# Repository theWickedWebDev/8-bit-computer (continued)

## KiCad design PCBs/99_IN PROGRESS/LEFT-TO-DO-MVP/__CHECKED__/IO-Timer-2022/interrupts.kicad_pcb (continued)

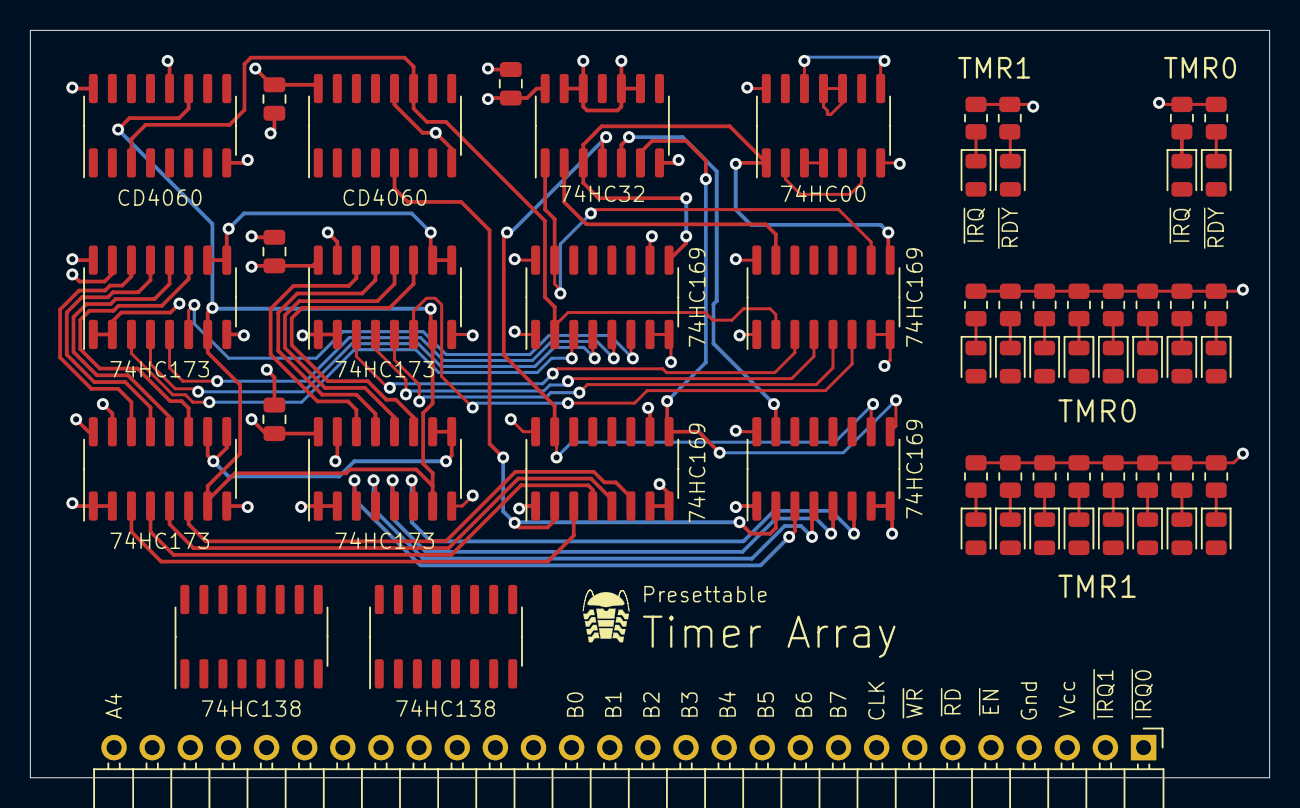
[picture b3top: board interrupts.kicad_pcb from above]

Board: 4 copper layers, 82.5 x 49.8 mm, 59 parts (0 on the bottom side), 83 nets.

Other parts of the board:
U9, U14: CD4060; SOIC-16_3.9x9.9mm_P1.27mm
U10, U11: 74LS173; SOIC-16_3.9x9.9mm_P1.27mm

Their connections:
/Reload Value Register/RELOAD0: U10.3 (Q0); also elsewhere on the board
/Reload Value Register/RELOAD1: U10.4 (Q1); also elsewhere on the board
/Reload Value Register/RELOAD2: U10.5 (Q2); also elsewhere on the board
/Reload Value Register/RELOAD3: U10.6 (Q3); also elsewhere on the board
/Reload Value Register/RELOAD4: U11.3 (Q0); also elsewhere on the board
/Reload Value Register/RELOAD5: U11.4 (Q1); also elsewhere on the board
/Reload Value Register/RELOAD6: U11.5 (Q2); also elsewhere on the board
/Reload Value Register/RELOAD7: U11.6 (Q3); also elsewhere on the board
BUS0: U10.14 (D0); also elsewhere on the board
BUS1: U10.13 (D1); also elsewhere on the board
BUS2: U10.12 (D2); also elsewhere on the board
BUS3: U10.11 (D3); also elsewhere on the board
BUS4: U11.14 (D0); also elsewhere on the board
BUS5: U11.13 (D1); also elsewhere on the board
BUS6: U11.12 (D2); also elsewhere on the board
BUS7: U11.11 (D3); also elsewhere on the board
CPU_CLOCK: U9.11 (I), U10.7 (Cp), U11.7 (Cp); also elsewhere on the board
GND: U9.8 (GND), U9.12 (RESET), U10.1 (Oe1), U10.2 (Oe2), U10.8 (GND), U10.15 (Mr), U11.1 (Oe1), U11.2 (Oe2), U11.8 (GND), U11.15 (Mr), U14.8 (GND), U14.12 (RESET); also elsewhere on the board
VCC: U9.16 (VCC), U10.16 (VCC), U11.16 (VCC), U14.16 (VCC); also elsewhere on the board
~SCLK8192: U9.3 (Q14), U14.11 (I); also elsewhere on the board
~SCLK131072: U14.5 (Q5); also elsewhere on the board
~SET_RELOAD_VALUE0: U10.9 (E1), U10.10 (E2), U11.9 (E1), U11.10 (E2); also elsewhere on the board

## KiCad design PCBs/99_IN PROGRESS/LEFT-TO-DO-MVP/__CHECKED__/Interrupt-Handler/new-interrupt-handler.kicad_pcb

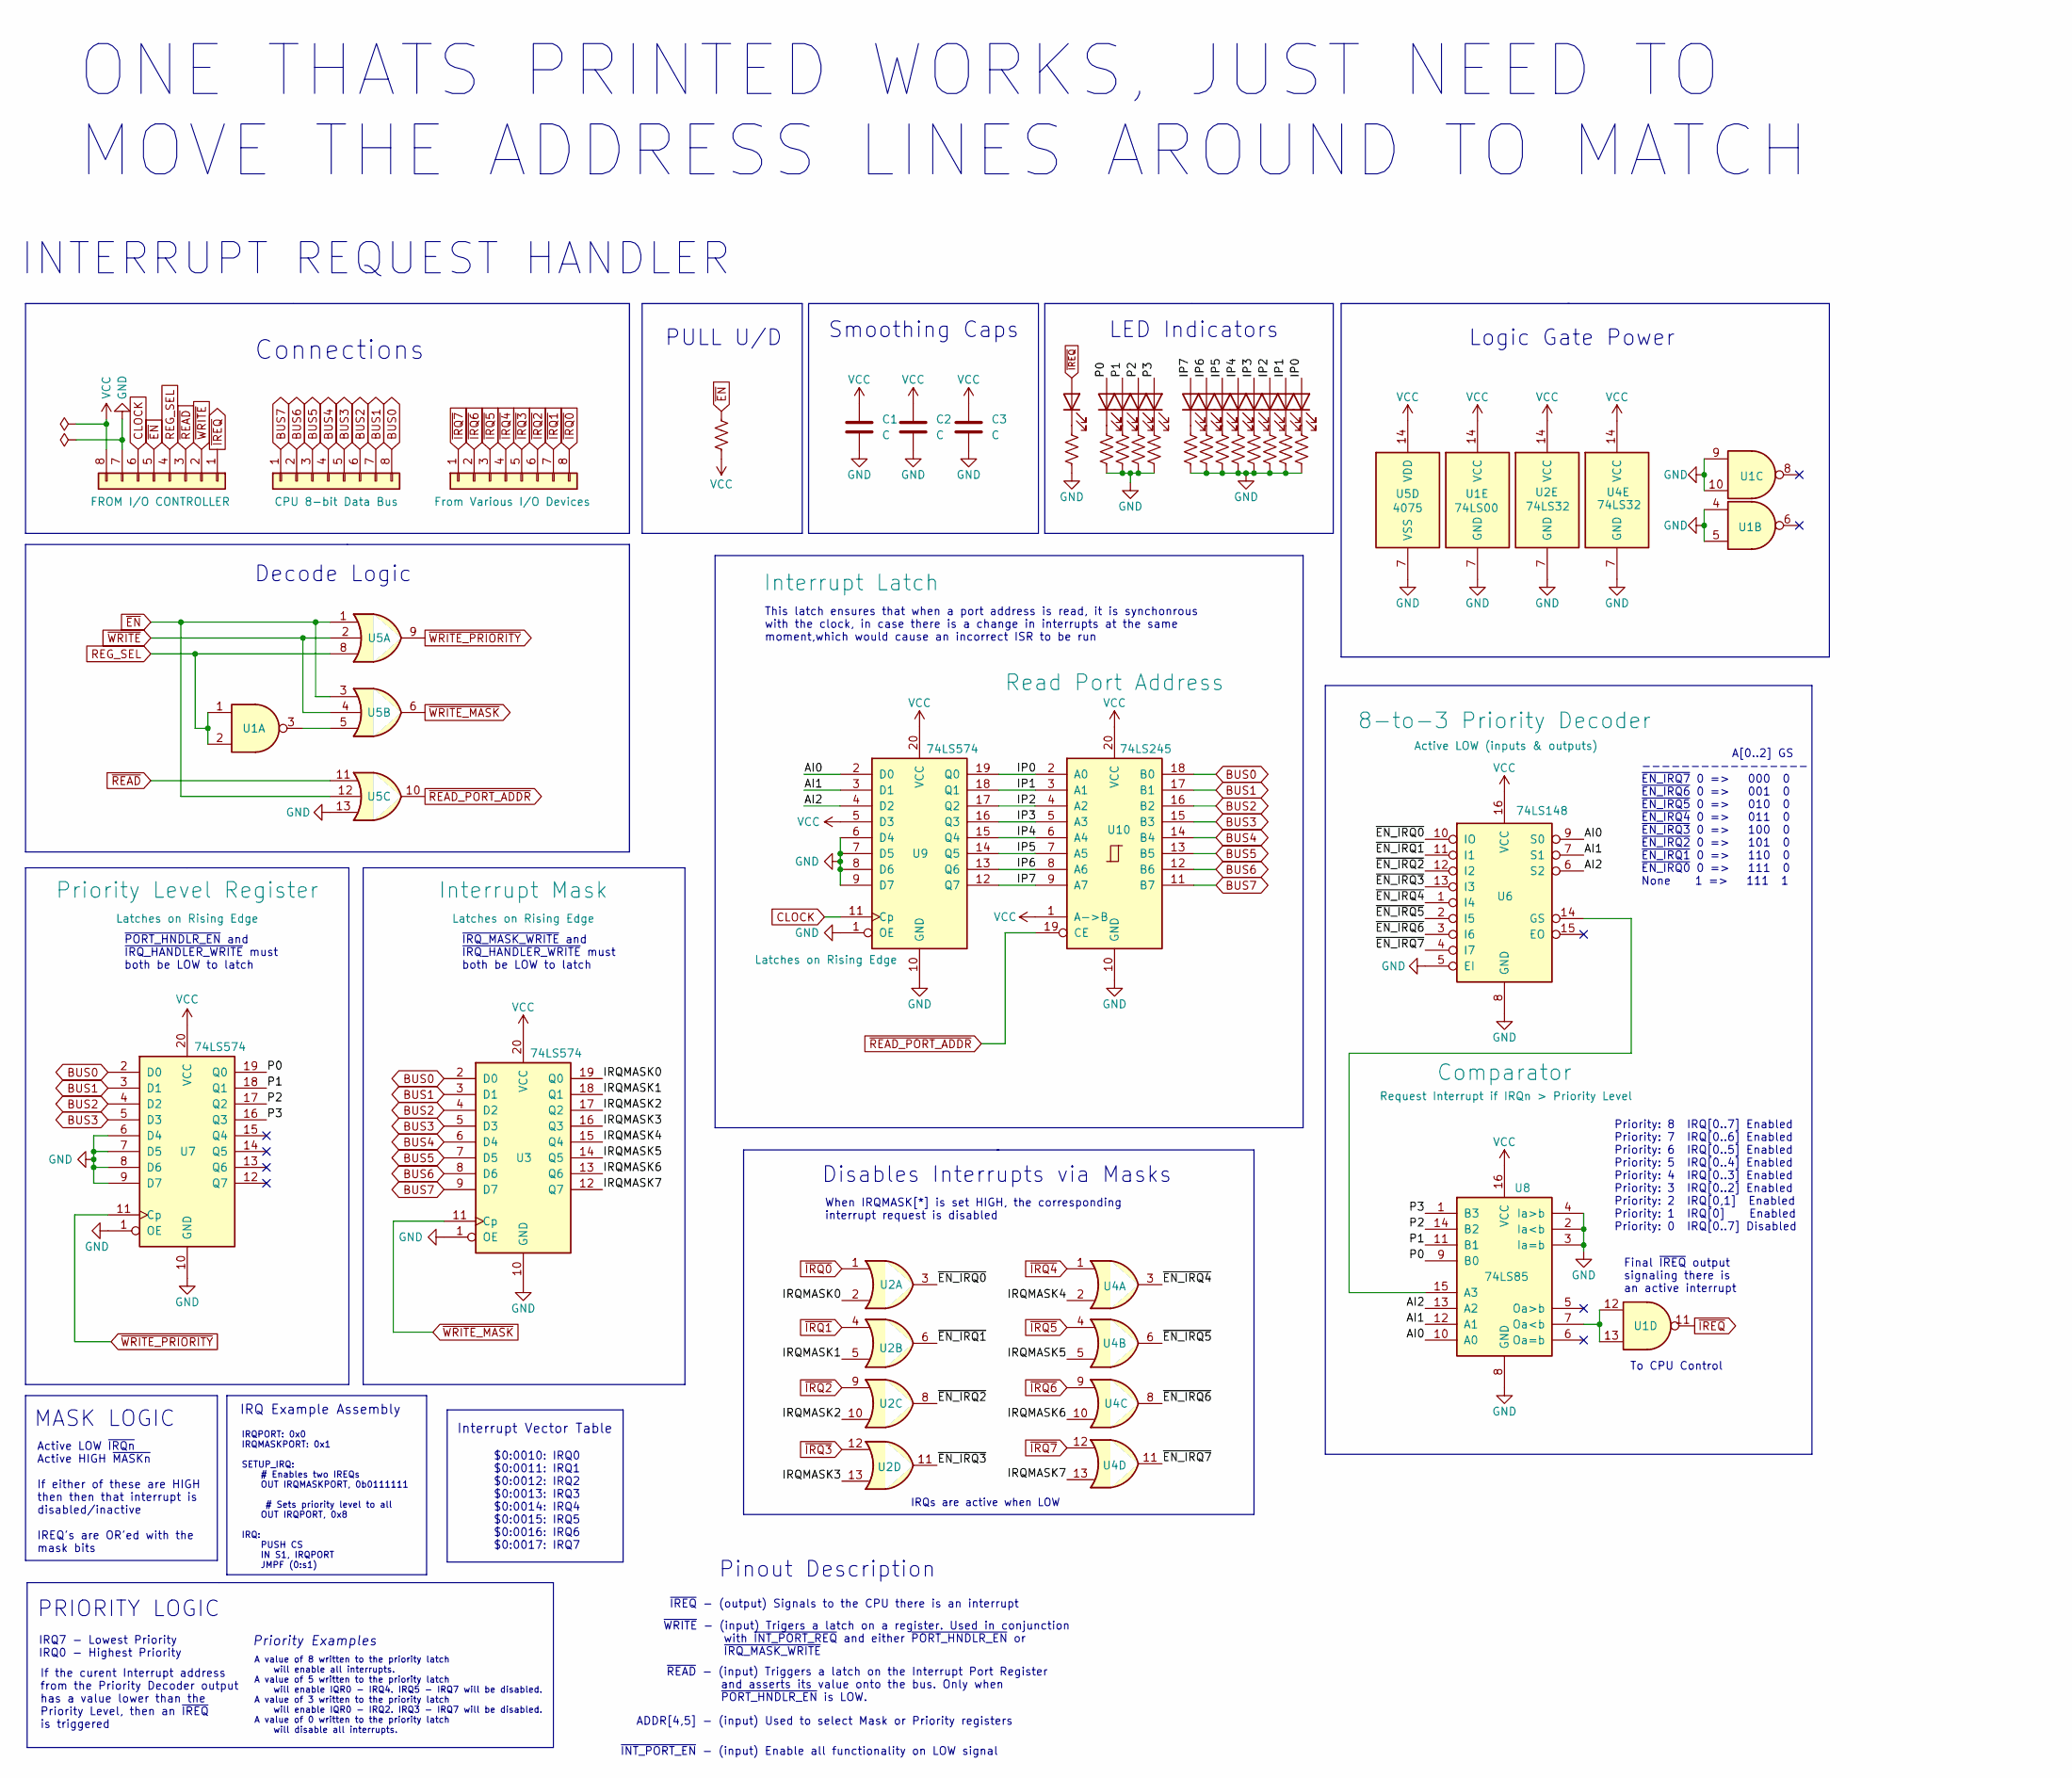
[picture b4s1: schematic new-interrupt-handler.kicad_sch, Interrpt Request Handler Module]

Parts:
C1, C2, C3: C; C_0805_2012Metric
D1, D2, D3, D4, D5, D6, D7, D8, D9, D10, D11, D12, D13: LED; LED_0805_2012Metric
J1, J2, J3: Conn_01x08; PinHeader_1x08_P2.54mm_Vertical
R1, R2, R3, R4, R5, R6, R7, R8, R9, R10, R11, R12, R13, R14: R_US; R_0805_2012Metric
U1: 74LS00; TSSOP-14_4.4x5mm_P0.65mm
U2, U4: 74LS32; TSSOP-14_4.4x5mm_P0.65mm
U3, U7, U9: 74LS574; SO-20_5.3x12.6mm_P1.27mm
U5: 4075
U6: 74LS148; SOIC-16_4.55x10.3mm_P1.27mm
U8: 74LS85; SOIC-16_4.55x10.3mm_P1.27mm
U10: 74LS245; TSSOP-20_4.4x6.5mm_P0.65mm

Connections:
/AI0: U6.9 (S0), U8.10 (A0), U9.2 (D0)
/AI1: U6.7 (S1), U8.12 (A1), U9.3 (D1)
/AI2: U6.6 (S2), U8.13 (A2), U9.4 (D2)
/IP0: D13.2 (A), U9.19 (Q0), U10.2 (A0)
/IP1: D12.2 (A), U9.18 (Q1), U10.3 (A1)
/IP2: D11.2 (A), U9.17 (Q2), U10.4 (A2)
/IP3: D10.2 (A), U9.16 (Q3), U10.5 (A3)
/IP4: D9.2 (A), U9.15 (Q4), U10.6 (A4)
/IP5: D8.2 (A), U9.14 (Q5), U10.7 (A5)
/IP6: D7.2 (A), U9.13 (Q6), U10.8 (A6)
/IP7: D6.2 (A), U9.12 (Q7), U10.9 (A7)
/IRQMASK0: U2.2, U3.19 (Q0)
/IRQMASK1: U2.5, U3.18 (Q1)
/IRQMASK2: U2.10, U3.17 (Q2)
/IRQMASK3: U2.13, U3.16 (Q3)
/IRQMASK4: U3.15 (Q4), U4.2
/IRQMASK5: U3.14 (Q5), U4.5
/IRQMASK6: U3.13 (Q6), U4.10
/IRQMASK7: U3.12 (Q7), U4.13
/P0: D2.2 (A), U7.19 (Q0), U8.9 (B0)
/P1: D3.2 (A), U7.18 (Q1), U8.11 (B1)
/P2: D4.2 (A), U7.17 (Q2), U8.14 (B2)
/P3: D5.2 (A), U7.16 (Q3), U8.1 (B3)
/~EN_IRQ0: U2.3, U6.10 (IO)
/~EN_IRQ1: U2.6, U6.11 (I1)
/~EN_IRQ2: U2.8, U6.12 (I2)
/~EN_IRQ3: U2.11, U6.13 (I3)
/~EN_IRQ4: U4.3, U6.1 (I4)
/~EN_IRQ5: U4.6, U6.2 (I5)
/~EN_IRQ6: U4.8, U6.3 (I6)
/~EN_IRQ7: U4.11, U6.4 (I7)
BUS0: J2.8, U3.2 (D0), U7.2 (D0), U10.18 (B0)
BUS1: J2.7, U3.3 (D1), U7.3 (D1), U10.17 (B1)
BUS2: J2.6, U3.4 (D2), U7.4 (D2), U10.16 (B2)
BUS3: J2.5, U3.5 (D3), U7.5 (D3), U10.15 (B3)
BUS4: J2.4, U3.6 (D4), U10.14 (B4)
BUS5: J2.3, U3.7 (D5), U10.13 (B5)
BUS6: J2.2, U3.8 (D6), U10.12 (B6)
BUS7: J2.1, U3.9 (D7), U10.11 (B7)
CLOCK: J1.6, U9.11 (Cp)
GND: C1.2, C2.2, C3.2, J1.7, R1.2, R2.2, R3.2, R4.2, R5.2, R6.2, R7.2, R8.2, R9.2, R10.2, R11.2, R12.2, R13.2, U1.4, U1.5, U1.7 (GND), U1.9, U1.10, U2.7 (GND), U3.1 (OE), U3.10 (GND), U4.7 (GND), U5.7 (VSS), U5.13, U6.5 (EI), U6.8 (GND), U7.1 (OE), U7.6 (D4), U7.7 (D5), U7.8 (D6), U7.9 (D7), U7.10 (GND), U8.2 (Ia<b), U8.3 (Ia=b), U8.4 (Ia>b), U8.8 (GND), U9.1 (OE), U9.6 (D4), U9.7 (D5), U9.8 (D6), U9.9 (D7), U9.10 (GND), U10.10 (GND)
unnamed: D1.1 (K), R1.1
unnamed: D2.1 (K), R2.1
unnamed: D3.1 (K), R3.1
unnamed: D4.1 (K), R4.1
unnamed: D5.1 (K), R5.1
unnamed: D6.1 (K), R6.1
unnamed: D7.1 (K), R7.1
unnamed: D8.1 (K), R8.1
unnamed: D9.1 (K), R9.1
unnamed: D10.1 (K), R10.1
unnamed: D11.1 (K), R11.1
unnamed: D12.1 (K), R12.1
unnamed: D13.1 (K), R13.1
unnamed: U1.3, U5.5
unnamed: U1.12, U1.13, U8.7 (Oa<b)
unnamed: U6.14 (GS), U8.15 (A3)
REG_SEL: J1.4, U1.1, U1.2, U5.8
VCC: C1.1, C2.1, C3.1, J1.8, R14.2, U1.14 (VCC), U2.14 (VCC), U3.20 (VCC), U4.14 (VCC), U5.14 (VDD), U6.16 (VCC), U7.20 (VCC), U8.16 (VCC), U9.5 (D3), U9.20 (VCC), U10.1 (A->B), U10.20 (VCC)
~EN: J1.5, R14.1, U5.1, U5.3, U5.12
~IREQ: D1.2 (A), J1.1, U1.11
~IRQ0: J3.8, U2.1
~IRQ1: J3.7, U2.4
~IRQ2: J3.6, U2.9
~IRQ3: J3.5, U2.12
~IRQ4: J3.4, U4.1
~IRQ5: J3.3, U4.4
~IRQ6: J3.2, U4.9
~IRQ7: J3.1, U4.12
~READ_PORT_ADDR: U5.10, U10.19 (CE)
~READ: J1.3, U5.11
~WRITE_MASK: U3.11 (Cp), U5.6
~WRITE_PRIORITY: U5.9, U7.11 (Cp)
~WRITE: J1.2, U5.2, U5.4

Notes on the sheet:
When IRQMASK[*] is set HIGH, the corresponding interrupt request is disabled
Disables Interrupts via Masks
IRQPORT: 0x0 IRQMASKPORT: 0x1 SETUP_IRQ: # Enables two IREQs OUT IRQMASKPORT, 0b0111111 # Sets priority level to all OUT IRQPORT, 0x8 IRQ: PUSH CS IN S1, IRQPORT JMPF (0:s1)
ONE THATS PRINTED WORKS, JUST NEED TO MOVE THE ADDRESS LINES AROUND TO MATCH
~{IRQ_MASK_WRITE} and ~{IRQ_HANDLER_WRITE} must both be LOW to latch
A[0..2] GS ----------------- ~{EN_IRQ7} 0 => 000 0 ~{EN_IRQ6} 0 => 001 0 ~{EN_IRQ5} 0 => 010 0 ~{EN_IRQ4} 0 => 011 0 ~{EN_IRQ3} 0 => 100 0 ~{EN_IRQ2} 0 => 101 0 ~{EN_IRQ1} 0 => 110 0 ~{EN_IRQ0} 0 => 111 0 None 1 => 111 1
Priority: 8 IRQ[0..7] Enabled Priority: 7 IRQ[0..6] Enabled Priority: 6 IRQ[0..5] Enabled Priority: 5 IRQ[0..4] Enabled Priority: 4 IRQ[0..3] Enabled Priority: 3 IRQ[0..2] Enabled Priority: 2 IRQ[0,1] Enabled Priority: 1 IRQ[0] Enabled Priority: 0 IRQ[0..7] Disabled
INTERRUPT REQUEST HANDLER
~{INT_PORT_EN} - (input) Enable all functionality on LOW signal
Pinout Description
LED Indicators
To CPU Control
IRQs are active when LOW
PULL U/D
$0:0010: IRQ0 $0:0011: IRQ1 $0:0012: IRQ2 $0:0013: IRQ3 $0:0014: IRQ4 $0:0015: IRQ5 $0:0016: IRQ6 $0:0017: IRQ7
~{WRITE} - (input) Trigers a latch on a register. Used in conjunction with ~{INT_PORT_REQ} and either ~{PORT_HNDLR_EN} or ~{IRQ_MASK_WRITE}
Logic Gate Power
~{IREQ} - (output) Signals to the CPU there is an interrupt
IRQ7 - Lowest Priority IRQ0 - Highest Priority
If the curent Interrupt address from the Priority Decoder output has a value lower than the Priority Level, then an ~{IREQ} is triggered
A value of 8 written to the priority latch will enable all interrupts. A value of 5 written to the priority latch will enable IQR0 - IRQ4. IRQ5 - IRQ7 will be disabled. A value of 3 written to the priority latch will enable IQR0 - IRQ2. IRQ3 - IRQ7 will be disabled. A value of 0 written to the prio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
Active LOW ~{IRQn} Active HIGH ~{MASKn} If either of these are HIGH then then that interrupt is disabled/inactive IREQ's are OR'ed with the mask bits
ADDR[4,5] - (input) Used to select Mask or Priority registers
MASK LOGIC
This latch ensures that when a port address is read, it is synchonrous with the clock, in case there is a change in interrupts at the same moment,which would cause an incorrect ISR to be run
Smoothing Caps
IRQ Example Assembly
Final ~{IREQ} output signaling there is an active interrupt
Priority Examples
~{PORT_HNDLR_EN} and ~{IRQ_HANDLER_WRITE} must both be LOW to latch
PRIORITY LOGIC
Decode Logic
~{READ} - (input) Triggers a latch on the Interrupt Port Register and asserts its value onto the bus. Only when ~{PORT_HNDLR_EN} is LOW.
Connections
Interrupt Vector Table

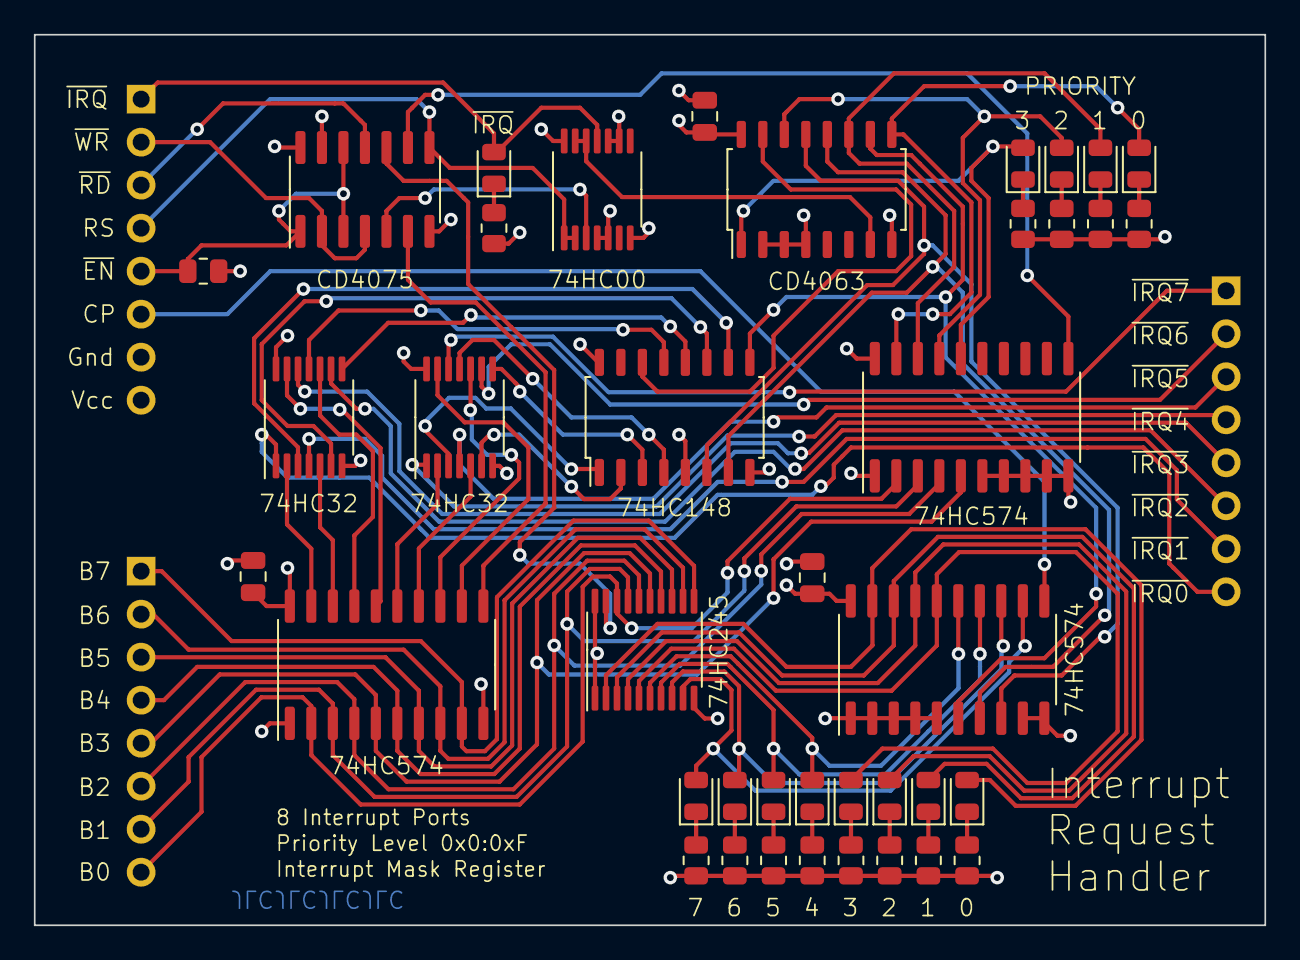
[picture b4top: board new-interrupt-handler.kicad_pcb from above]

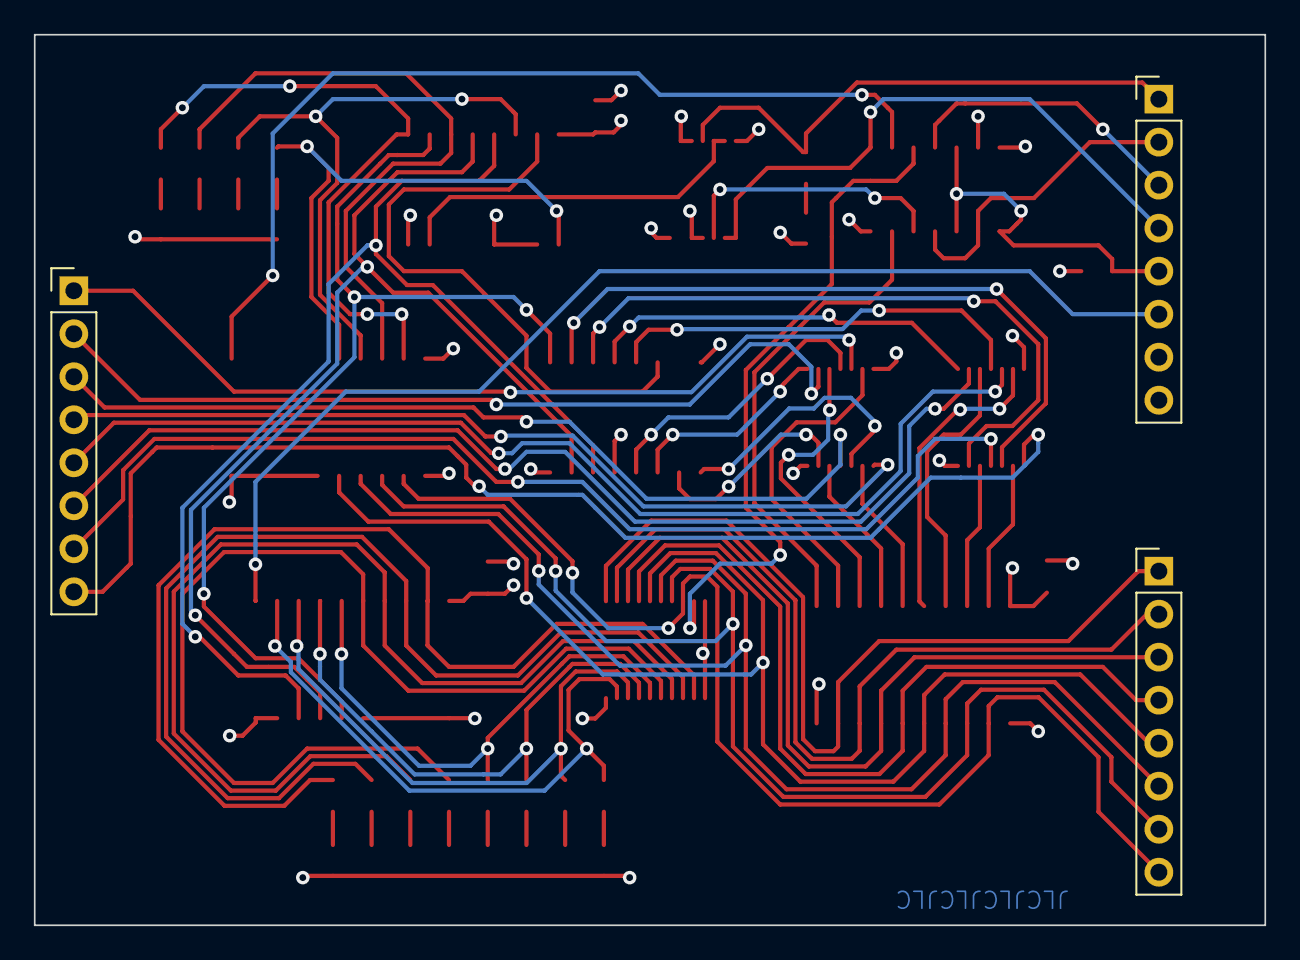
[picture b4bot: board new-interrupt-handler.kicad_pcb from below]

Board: 4 copper layers, 72.7 x 52.6 mm, 43 parts (3 on the bottom side), 74 nets.

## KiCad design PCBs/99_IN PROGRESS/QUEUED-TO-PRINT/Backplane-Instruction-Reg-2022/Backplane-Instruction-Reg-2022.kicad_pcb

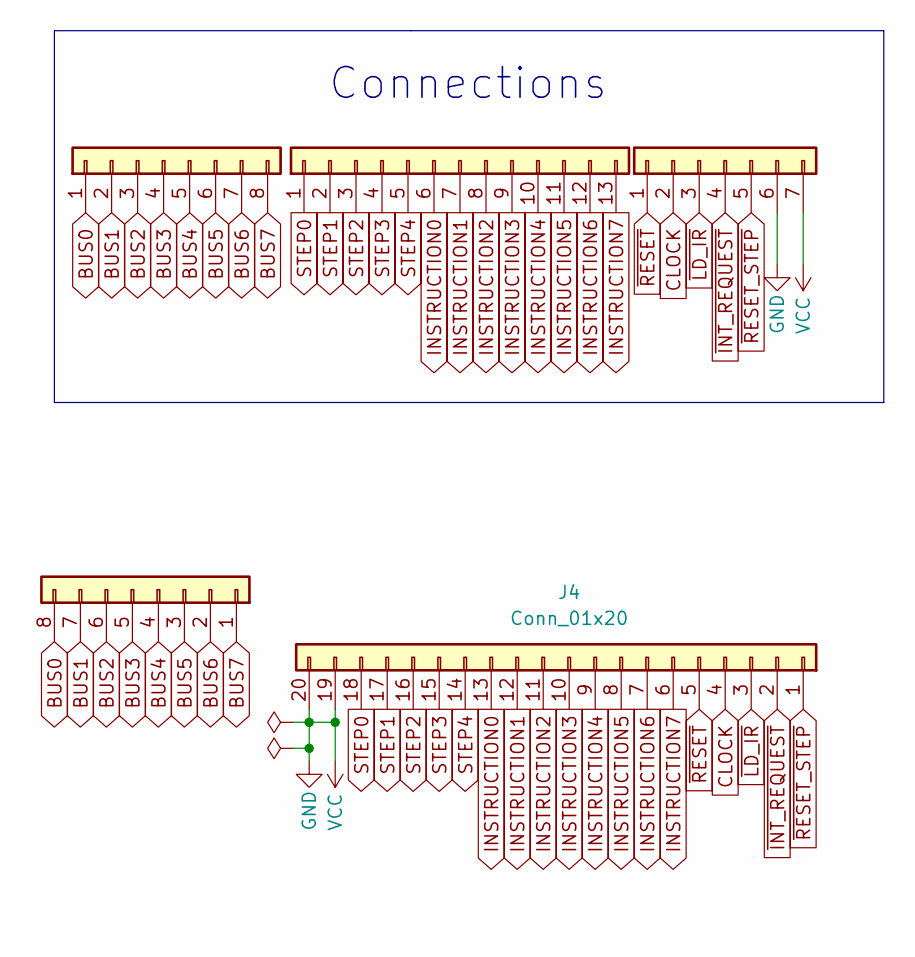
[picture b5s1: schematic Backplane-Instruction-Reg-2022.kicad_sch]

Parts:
J1: Conn_01x08; PinHeader_1x08_P2.54mm_Horizontal
J2: Conn_01x08; PinSocket_1x08_P2.54mm_Vertical
J3: Conn_01x13; PinSocket_1x13_P2.54mm_Vertical
J4: Conn_01x20; PinHeader_1x20_P2.54mm_Horizontal
J5: Conn_01x07; PinSocket_1x07_P2.54mm_Vertical

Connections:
BUS0: J1.8, J2.1
BUS1: J1.7, J2.2
BUS2: J1.6, J2.3
BUS3: J1.5, J2.4
BUS4: J1.4, J2.5
BUS5: J1.3, J2.6
BUS6: J1.2, J2.7
BUS7: J1.1, J2.8
CLOCK: J4.4, J5.2
GND: J4.19, J4.20, J5.6, J5.7
INSTRUCTION0: J3.6, J4.13
INSTRUCTION1: J3.7, J4.12
INSTRUCTION2: J3.8, J4.11
INSTRUCTION3: J3.9, J4.10
INSTRUCTION4: J3.10, J4.9
INSTRUCTION5: J3.11, J4.8
INSTRUCTION6: J3.12, J4.7
INSTRUCTION7: J3.13, J4.6
STEP0: J3.1, J4.18
STEP1: J3.2, J4.17
STEP2: J3.3, J4.16
STEP3: J3.4, J4.15
STEP4: J3.5, J4.14
~INT_REQUEST: J4.2, J5.4
~LD_IR: J4.3, J5.3
~RESET_STEP: J4.1, J5.5
~RESET: J4.5, J5.1

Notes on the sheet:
Connections

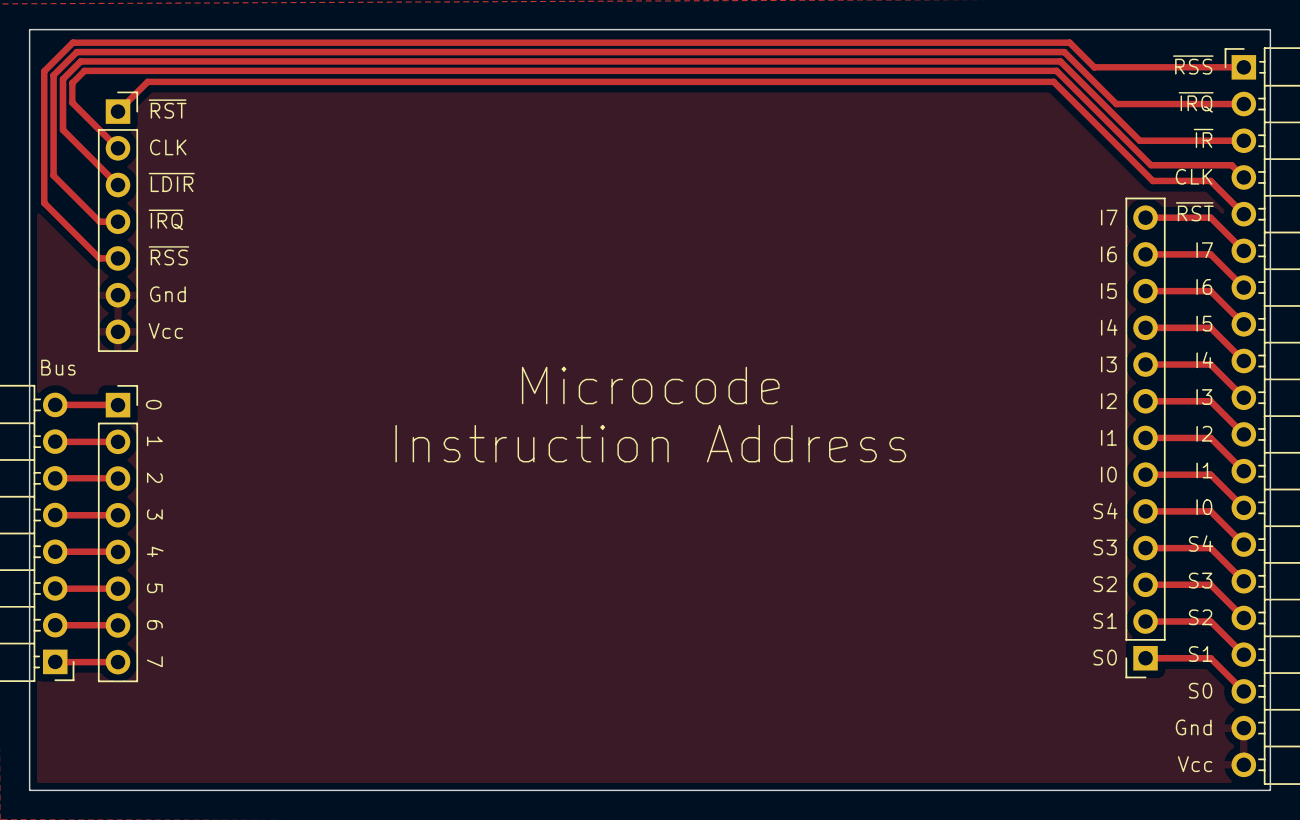
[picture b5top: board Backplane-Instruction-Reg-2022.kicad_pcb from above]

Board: 2 copper layers, 85.8 x 52.6 mm, 5 parts (0 on the bottom side), 27 nets.

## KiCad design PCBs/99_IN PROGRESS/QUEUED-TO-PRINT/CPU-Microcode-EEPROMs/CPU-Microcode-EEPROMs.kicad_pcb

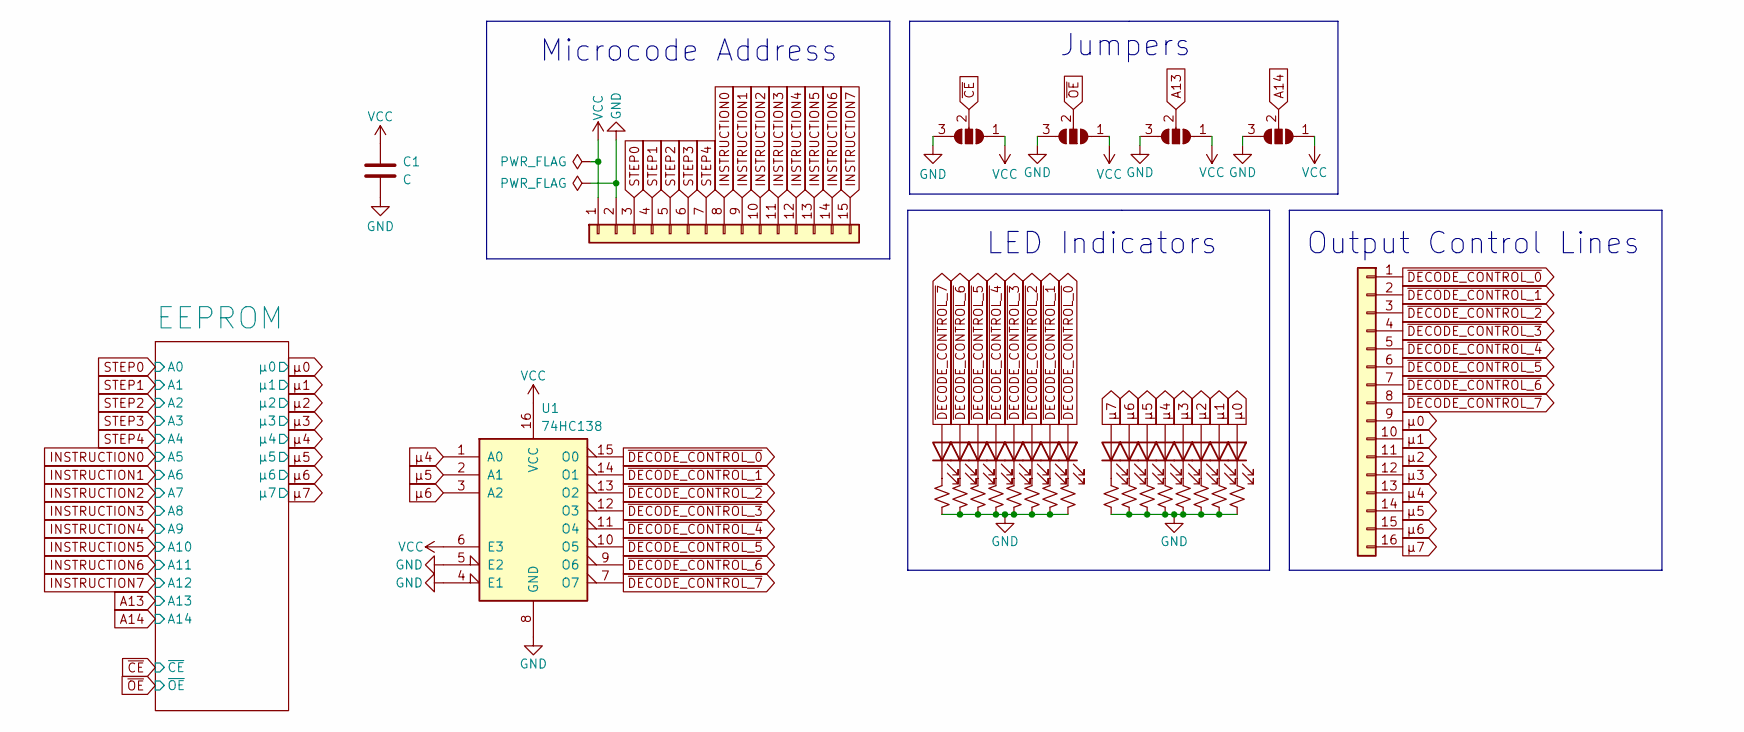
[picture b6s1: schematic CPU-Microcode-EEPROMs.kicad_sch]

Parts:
C1: C; C_0805_2012Metric
D1, D2, D3, D4, D5, D6, D7, D8, D9, D10, D11, D12, D13, D14, D15, D16: LED; LED_0805_2012Metric
J1: Conn_01x15; PinHeader_1x15_P2.54mm_Vertical
J2: Conn_01x16; PinHeader_1x16_P2.54mm_Vertical
JP1: ~{CE}; SolderJumper-3_P1.3mm_Open_RoundedPad1.0x1.5mm
JP2: ~{OE}; SolderJumper-3_P1.3mm_Open_RoundedPad1.0x1.5mm
JP3: A13; SolderJumper-3_P1.3mm_Open_RoundedPad1.0x1.5mm
JP4: A14; SolderJumper-3_P1.3mm_Open_RoundedPad1.0x1.5mm
R1, R2, R3, R4, R5, R6, R7, R8, R9, R10, R11, R12, R13, R14, R15, R16: R_Small_US; R_0805_2012Metric
U1: 74HC138; TSSOP-16_4.4x5mm_P0.65mm

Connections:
A13: JP3.2 (C); also elsewhere on the board
A14: JP4.2 (C); also elsewhere on the board
GND: C1.2, J1.2, JP1.3 (B), JP2.3 (B), JP3.3 (B), JP4.3 (B), R1.2, R2.2, R3.2, R4.2, R5.2, R6.2, R7.2, R8.2, R9.2, R10.2, R11.2, R12.2, R13.2, R14.2, R15.2, R16.2, U1.4 (E1), U1.5 (E2), U1.8 (GND); also elsewhere on the board
INSTRUCTION0: J1.8; also elsewhere on the board
INSTRUCTION1: J1.9; also elsewhere on the board
INSTRUCTION2: J1.10; also elsewhere on the board
INSTRUCTION3: J1.11; also elsewhere on the board
INSTRUCTION4: J1.12; also elsewhere on the board
INSTRUCTION5: J1.13; also elsewhere on the board
INSTRUCTION6: J1.14; also elsewhere on the board
INSTRUCTION7: J1.15; also elsewhere on the board
unnamed: D1.1 (K), R1.1
unnamed: D2.1 (K), R2.1
unnamed: D3.1 (K), R3.1
unnamed: D4.1 (K), R4.1
unnamed: D5.1 (K), R5.1
unnamed: D6.1 (K), R6.1
unnamed: D7.1 (K), R7.1
unnamed: D8.1 (K), R8.1
unnamed: D9.1 (K), R9.1
unnamed: D10.1 (K), R10.1
unnamed: D11.1 (K), R11.1
unnamed: D12.1 (K), R12.1
unnamed: D13.1 (K), R13.1
unnamed: D14.1 (K), R14.1
unnamed: D15.1 (K), R15.1
unnamed: D16.1 (K), R16.1
STEP0: J1.3; also elsewhere on the board
STEP1: J1.4; also elsewhere on the board
STEP2: J1.5; also elsewhere on the board
STEP3: J1.6; also elsewhere on the board
STEP4: J1.7; also elsewhere on the board
VCC: C1.1, J1.1, JP1.1 (A), JP2.1 (A), JP3.1 (A), JP4.1 (A), U1.6 (E3), U1.16 (VCC); also elsewhere on the board
~CE: JP1.2 (C); also elsewhere on the board
~DECODE_CONTROL_0: D8.2 (A), J2.1, U1.15 (O0)
~DECODE_CONTROL_1: D7.2 (A), J2.2, U1.14 (O1)
~DECODE_CONTROL_2: D6.2 (A), J2.3, U1.13 (O2)
~DECODE_CONTROL_3: D5.2 (A), J2.4, U1.12 (O3)
~DECODE_CONTROL_4: D4.2 (A), J2.5, U1.11 (O4)
~DECODE_CONTROL_5: D3.2 (A), J2.6, U1.10 (O5)
~DECODE_CONTROL_6: D2.2 (A), J2.7, U1.9 (O6)
~DECODE_CONTROL_7: D1.2 (A), J2.8, U1.7 (O7)
~OE: JP2.2 (C); also elsewhere on the board
μ0: D16.2 (A), J2.9; also elsewhere on the board
μ1: D15.2 (A), J2.10; also elsewhere on the board
μ2: D14.2 (A), J2.11; also elsewhere on the board
μ3: D13.2 (A), J2.12; also elsewhere on the board
μ4: D12.2 (A), J2.13, U1.1 (A0); also elsewhere on the board
μ5: D11.2 (A), J2.14, U1.2 (A1); also elsewhere on the board
μ6: D10.2 (A), J2.15, U1.3 (A2); also elsewhere on the board
μ7: D9.2 (A), J2.16; also elsewhere on the board

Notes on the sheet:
Output Control Lines
Microcode Address
LED Indicators
Jumpers

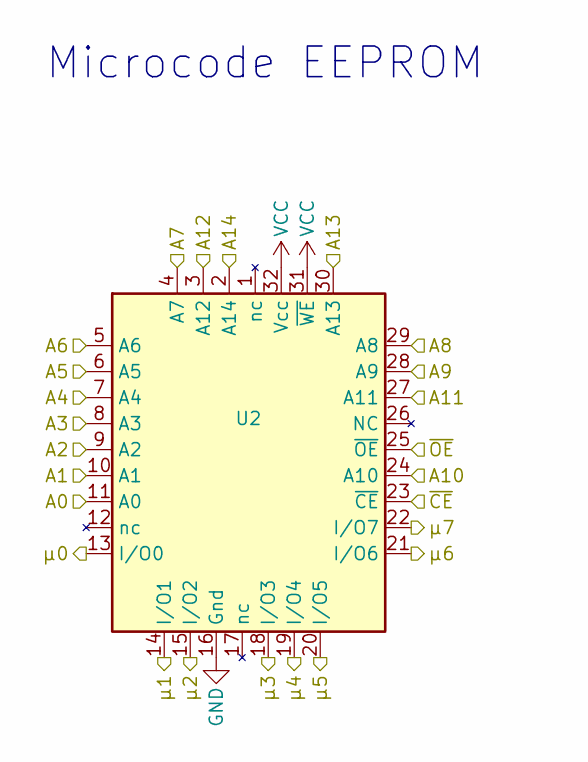
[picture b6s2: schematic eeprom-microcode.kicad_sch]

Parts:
U2: AT28C256; Socket-PLCC-32

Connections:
A13: U2.30 (A13); also elsewhere on the board
A14: U2.2 (A14); also elsewhere on the board
GND: U2.16 (Gnd); also elsewhere on the board
INSTRUCTION0: U2.6 (A5); also elsewhere on the board
INSTRUCTION1: U2.5 (A6); also elsewhere on the board
INSTRUCTION2: U2.4 (A7); also elsewhere on the board
INSTRUCTION3: U2.29 (A8); also elsewhere on the board
INSTRUCTION4: U2.28 (A9); also elsewhere on the board
INSTRUCTION5: U2.24 (A10); also elsewhere on the board
INSTRUCTION6: U2.27 (A11); also elsewhere on the board
INSTRUCTION7: U2.3 (A12); also elsewhere on the board
STEP0: U2.11 (A0); also elsewhere on the board
STEP1: U2.10 (A1); also elsewhere on the board
STEP2: U2.9 (A2); also elsewhere on the board
STEP3: U2.8 (A3); also elsewhere on the board
STEP4: U2.7 (A4); also elsewhere on the board
VCC: U2.31 (~WE), U2.32 (Vcc); also elsewhere on the board
~CE: U2.23 (~CE); also elsewhere on the board
~OE: U2.25 (~OE); also elsewhere on the board
μ0: U2.13 (I/O0); also elsewhere on the board
μ1: U2.14 (I/O1); also elsewhere on the board
μ2: U2.15 (I/O2); also elsewhere on the board
μ3: U2.18 (I/O3); also elsewhere on the board
μ4: U2.19 (I/O4); also elsewhere on the board
μ5: U2.20 (I/O5); also elsewhere on the board
μ6: U2.21 (I/O6); also elsewhere on the board
μ7: U2.22 (I/O7); also elsewhere on the board

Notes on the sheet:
Microcode EEPROM

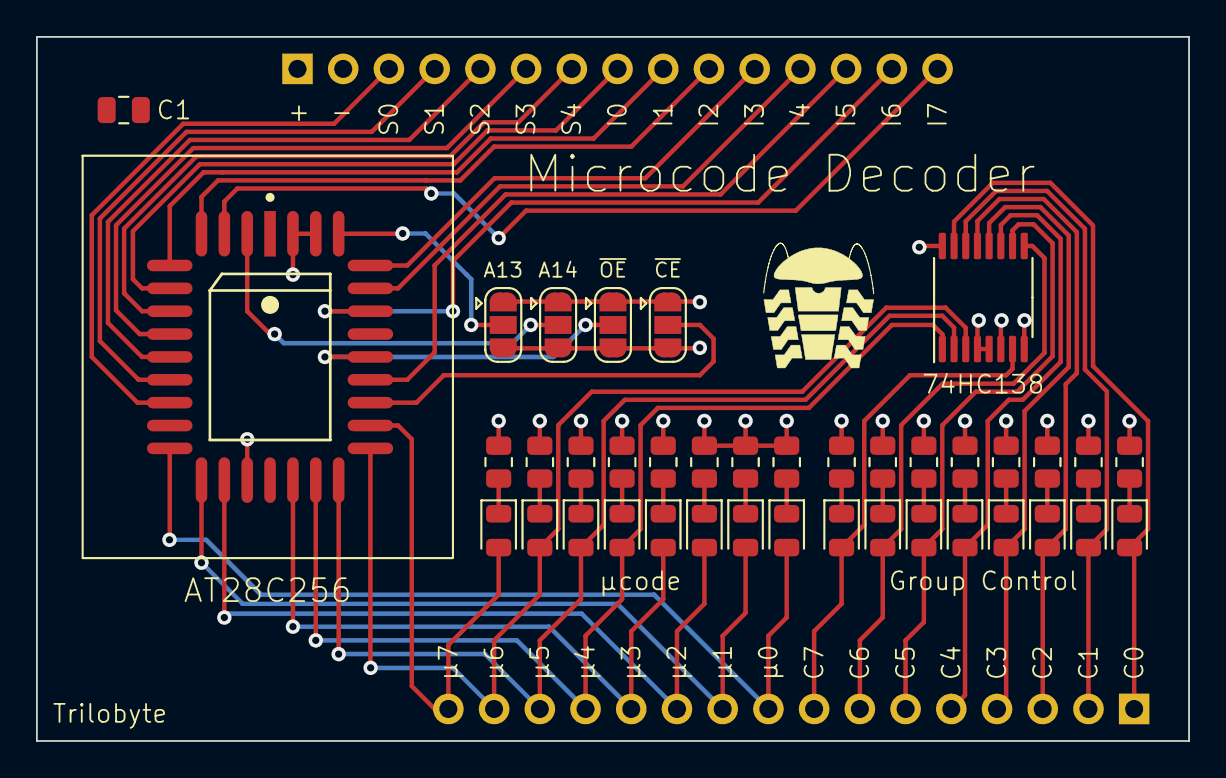
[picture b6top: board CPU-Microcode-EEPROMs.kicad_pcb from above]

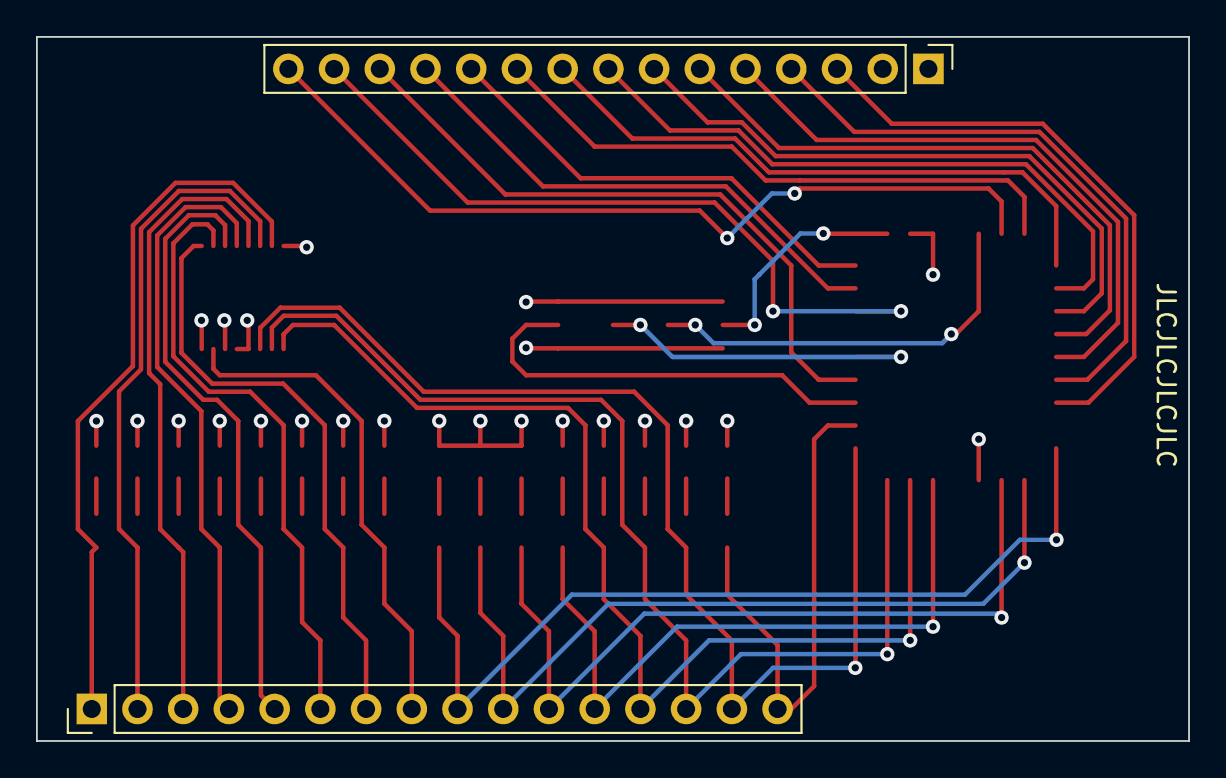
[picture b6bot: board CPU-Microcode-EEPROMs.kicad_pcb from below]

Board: 4 copper layers, 64.0 x 39.1 mm, 41 parts (2 on the bottom side), 51 nets.

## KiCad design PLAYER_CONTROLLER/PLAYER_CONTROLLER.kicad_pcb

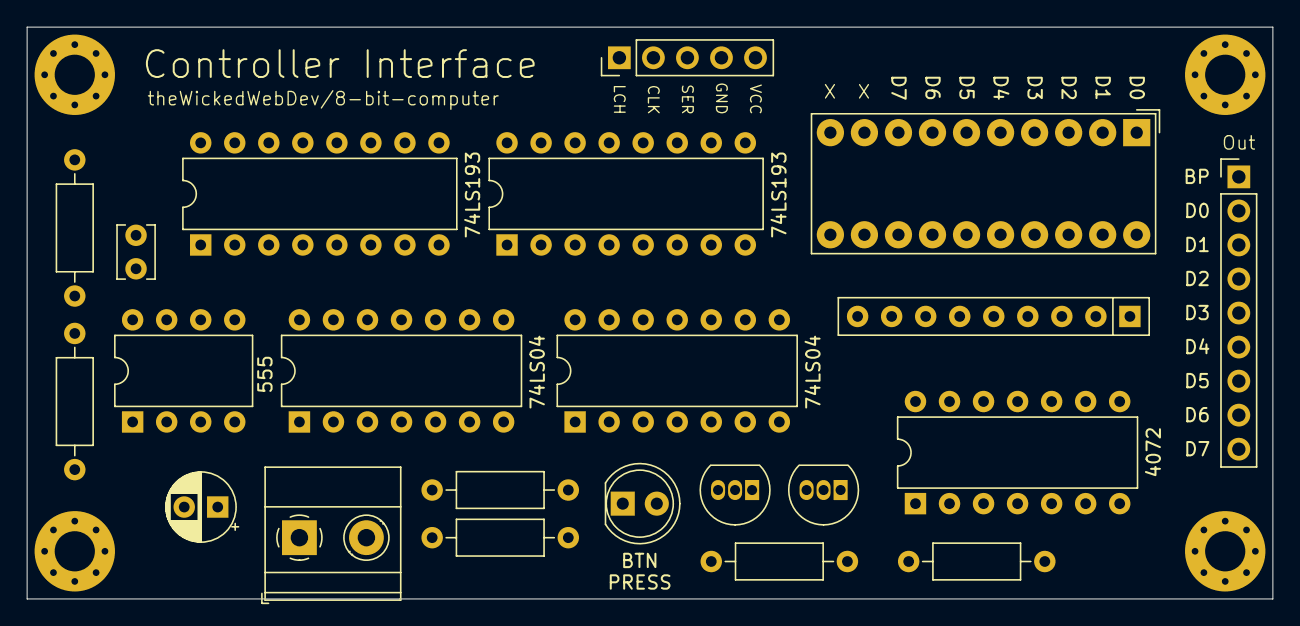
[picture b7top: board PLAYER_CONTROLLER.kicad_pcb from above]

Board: 2 copper layers, 93.0 x 42.7 mm, 22 parts (0 on the bottom side), 38 nets, no tracks yet.

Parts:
BAR1: HDSP-4830_2; HDSP-4830
C1: CP1_Small; C_Disc_D3.8mm_W2.6mm_P2.50mm
C2: CP1_Small; CP_Radial_D5.0mm_P2.50mm
D1: LED; LED_D5.0mm
J1: Screw_Terminal_01x02; TerminalBlock_Phoenix_MKDS-1,5-2_1x02_P5.00mm_Horizontal
J2: Conn_01x05; PinHeader_1x05_P2.54mm_Vertical
J3: Conn_01x09; PinHeader_1x09_P2.54mm_Vertical
Q1, Q2: PN2222A; TO-92_Inline
R1, R2, R3, R4, R5, R6: R_Small_US; R_Axial_DIN0207_L6.3mm_D2.5mm_P10.16mm_Horizontal
RN1: R_Network08_US; R_Array_SIP9
U1: LM555xN; DIP-8_W7.62mm
U2: 74LS193; DIP-16_W7.62mm
U3: 74HC595; DIP-16_W7.62mm
U4: 4072; DIP-14_W7.62mm
U5, U6: 74LS04; DIP-14_W7.62mm

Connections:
C_BTN_PRESS: D1.2, J3.1, Q1.1, Q2.1, R5.1
C_CLOCK: J2.2, U1.3, U2.5, U3.11
C_DATA: J2.3, U3.14
C_LATCH: J2.1, U2.7, U3.10, U3.12
D0: BAR1.1, J3.2, U4.12, U5.2
D1: BAR1.2, J3.3, U4.11, U5.4
D2: BAR1.3, J3.4, U4.10, U5.6
D3: BAR1.4, J3.5, U4.9, U5.8
D4: BAR1.5, J3.6, U4.5, U5.10
D5: BAR1.6, J3.7, U4.4, U5.12
D6: BAR1.7, J3.8, U4.3, U6.2
D7: BAR1.8, J3.9, U4.2, U6.4
GND: C1.2, C2.2, J1.2, J2.4, R5.2, R6.1, RN1.1, U1.1, U2.1, U2.8, U2.9, U2.10, U2.14, U2.15, U3.8, U3.13, U4.7, U5.7, U6.7
unnamed: BAR1.13, RN1.9
unnamed: BAR1.14, RN1.8
unnamed: BAR1.15, RN1.7
unnamed: BAR1.16, RN1.6
unnamed: BAR1.17, RN1.5
unnamed: BAR1.18, RN1.4
unnamed: BAR1.19, RN1.3
unnamed: BAR1.20, RN1.2
unnamed: C1.1, R2.2, U1.2, U1.6
unnamed: D1.1, R6.2
unnamed: Q1.2, R3.1
unnamed: Q2.2, R4.1
unnamed: R1.2, R2.1, U1.7
unnamed: R3.2, U4.1
unnamed: R4.2, U4.13
unnamed: U2.11, U2.12
unnamed: U3.1, U5.3
unnamed: U3.2, U5.5
unnamed: U3.3, U5.9
unnamed: U3.4, U5.11
unnamed: U3.5, U5.13
unnamed: U3.6, U6.1
unnamed: U3.7, U6.3
unnamed: U3.15, U5.1
VCC: C2.1, J1.1, J2.5, Q1.3, Q2.3, R1.1, U1.4, U1.8, U2.4, U2.16, U3.16, U4.14, U5.14, U6.14
